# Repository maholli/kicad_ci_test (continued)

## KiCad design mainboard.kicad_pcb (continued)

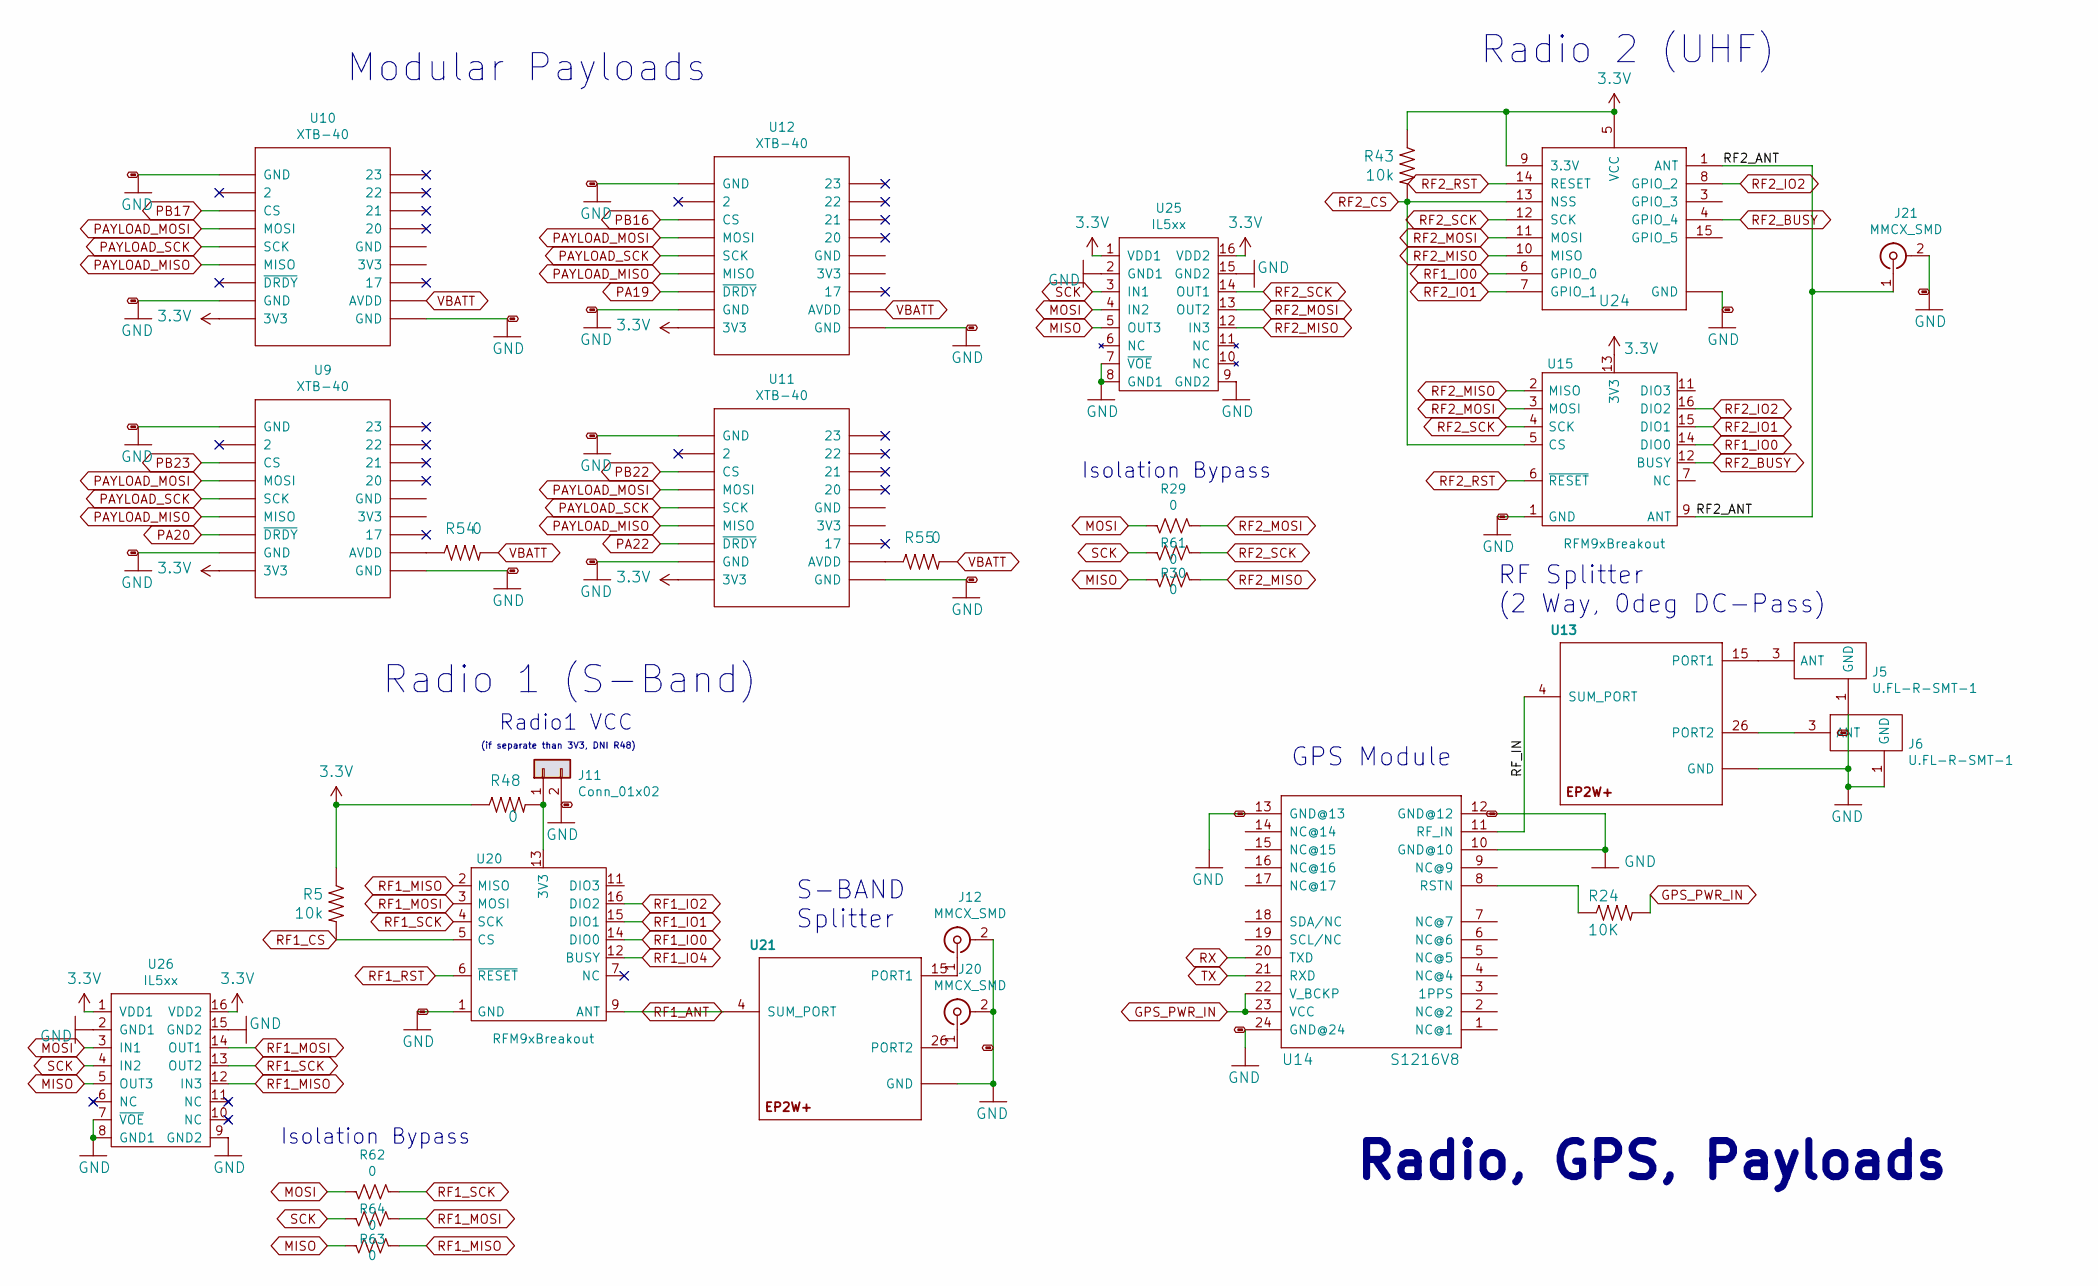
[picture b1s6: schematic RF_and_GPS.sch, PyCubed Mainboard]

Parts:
J5, J6: U.FL-R-SMT-1; Manufacturer_Part_Number U.FL-R-SMT-1
J11: Conn_01x02; PinHeader_1x02_P2.54mm_Vertical
J12, J20, J21: MMCX_SMD; 0734152063
R5, R43: 10k; R_0603_1608Metric
R24: 10K; R_0603_1608Metric
R29, R30, R48, R54, R55, R61, R62, R63, R64: 0; R_0603_1608Metric
U9, U10, U11, U12: XTB-40; XTB28_MEZ
U13, U21: EP2W+; QFN32-5X5MM
U14: S1216V8; S1216_24PIN_PACKAGE
U15, U20: RFM9xBreakout; HOPERF_RFM9XW_SMD
U24: RFM98PW
U25, U26: IL5xx; SOIC-16_IL5xx

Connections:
3.3V: R5.1, R43.1, R48.1, U9.9 (3V3), U10.9 (3V3), U11.9 (3V3), U12.9 (3V3), U15.13 (3V3), U24.5 (VCC), U24.9 (3.3V), U25.1 (VDD1), U25.16 (VDD2), U26.1 (VDD1), U26.16 (VDD2); also elsewhere on the board
/RF and GPS/RF2_ANT: J21.1 (In), U15.9 (ANT), U24.1 (ANT)
/RF and GPS/RF_IN: U13.4 (SUM_PORT), U14.11 (RF_IN)
GND: J5.1 (GND), J5.2, J6.1 (GND), J6.2, J11.2, J12.2 (Ext), J12.3, J12.4, J12.5, J20.2 (Ext), J20.3, J20.4, J20.5, J21.2 (Ext), J21.3, J21.4, J21.5, U9.1 (GND), U9.8 (GND), U9.10 (GND), U9.15 (GND), U10.1 (GND), U10.8 (GND), U10.10 (GND), U10.15 (GND), U11.1 (GND), U11.8 (GND), U11.10 (GND), U11.15 (GND), U12.1 (GND), U12.8 (GND), U12.10 (GND), U12.15 (GND), U13.1 (GND), U13.2 (GND), U13.3 (GND), U13.5 (GND), U13.6 (GND), U13.7 (GND), U13.8 (GND), U13.9 (GND), U13.10 (GND), U13.11 (GND), U13.12 (GND), U13.13 (GND), U13.14 (GND), U13.16 (GND), U13.17 (GND), U13.18 (GND), U13.19 (GND), U13.20 (GND), U13.21 (GND), U13.22 (GND), U13.23 (GND), U13.24 (GND), U13.25 (GND), U13.27 (GND), U13.28 (GND), U13.29 (GND), U13.30 (GND), U13.31 (GND), U13.32 (GND), U13.EP (GND), U14.10 (GND@10), U14.12 (GND@12), U14.13 (GND@13), U14.24 (GND@24), U15.1 (GND), U15.8 (GND), U15.10 (GND), U20.1 (GND), U20.8 (GND), U20.10 (GND), U21.1 (GND), U21.2 (GND), U21.3 (GND), U21.5 (GND), U21.6 (GND), U21.7 (GND), U21.8 (GND), U21.9 (GND), U21.10 (GND), U21.11 (GND), U21.12 (GND), U21.13 (GND), U21.14 (GND), U21.16 (GND), U21.17 (GND), U21.18 (GND), U21.19 (GND), U21.20 (GND), U21.21 (GND), U21.22 (GND), U21.23 (GND), U21.24 (GND), U21.25 (GND), U21.27 (GND), U21.28 (GND), U21.29 (GND), U21.30 (GND), U21.31 (GND), U21.32 (GND), U21.EP (GND), U24.2 (GND), U24.16 (GND), U25.2 (GND1), U25.7 (~VOE), U25.8 (GND1), U25.9 (GND2), U25.15 (GND2), U26.2 (GND1), U26.7 (~VOE), U26.8 (GND1), U26.9 (GND2), U26.15 (GND2); also elsewhere on the board
GPS_PWR_IN: R24.2, U14.22 (V_BCKP), U14.23 (VCC); also elsewhere on the board
MISO: R61.1, R64.1, U25.5 (OUT3), U26.5 (OUT3); also elsewhere on the board
MOSI: R29.1, R62.1, U25.4 (IN2), U26.3 (IN1); also elsewhere on the board
unnamed: J5.3 (ANT), U13.15 (PORT1)
unnamed: J6.3 (ANT), U13.26 (PORT2)
unnamed: J11.1, R48.2, U20.13 (3V3)
unnamed: J12.1 (In), U21.15 (PORT1)
unnamed: J20.1 (In), U21.26 (PORT2)
unnamed: R24.1, U14.8 (RSTN)
unnamed: R54.1, U9.11 (AVDD), U9.16 (AVDD)
unnamed: R55.1, U11.11 (AVDD), U11.16 (AVDD)
PA19: U12.7 (~DRDY); also elsewhere on the board
PA20: U9.7 (~DRDY); also elsewhere on the board
PA22: U11.7 (~DRDY); also elsewhere on the board
PAYLOAD_MISO: U9.6 (MISO), U10.6 (MISO), U11.6 (MISO), U12.6 (MISO); also elsewhere on the board
PAYLOAD_MOSI: U9.4 (MOSI), U10.4 (MOSI), U11.4 (MOSI), U12.4 (MOSI); also elsewhere on the board
PAYLOAD_SCK: U9.5 (SCK), U10.5 (SCK), U11.5 (SCK), U12.5 (SCK); also elsewhere on the board
PB16: U12.3 (CS); also elsewhere on the board
PB17: U10.3 (CS); also elsewhere on the board
PB22: U11.3 (CS); also elsewhere on the board
PB23: U9.3 (CS); also elsewhere on the board
RF1_ANT: U20.9 (ANT), U21.4 (SUM_PORT)
RF1_CS: R5.2, U20.5 (CS); also elsewhere on the board
RF1_IO0: U15.14 (DIO0), U20.14 (DIO0), U24.6 (GPIO_0); also elsewhere on the board
RF1_IO1: U20.15 (DIO1)
RF1_IO2: U20.16 (DIO2)
RF1_IO4: U20.12 (BUSY); also elsewhere on the board
RF1_MISO: R64.2, U20.2 (MISO), U26.12 (IN3)
RF1_MOSI: R63.2, U20.3 (MOSI), U26.14 (OUT1)
RF1_RST: U20.6 (~RESET); also elsewhere on the board
RF1_SCK: R62.2, U20.4 (SCK), U26.13 (OUT2)
RF2_BUSY: U15.12 (BUSY), U24.4 (GPIO_4); also elsewhere on the board
RF2_CS: R43.2, U15.5 (CS), U24.13 (NSS); also elsewhere on the board
RF2_IO1: U15.15 (DIO1), U24.7 (GPIO_1); also elsewhere on the board
RF2_IO2: U15.16 (DIO2), U24.8 (GPIO_2)
RF2_MISO: R61.2, U15.2 (MISO), U24.10 (MISO), U25.12 (IN3); also elsewhere on the board
RF2_MOSI: R29.2, U15.3 (MOSI), U24.11 (MOSI), U25.13 (OUT2); also elsewhere on the board
RF2_RST: U15.6 (~RESET), U24.14 (RESET); also elsewhere on the board
RF2_SCK: R30.2, U15.4 (SCK), U24.12 (SCK), U25.14 (OUT1); also elsewhere on the board
RX: U14.20 (TXD); also elsewhere on the board
SCK: R30.1, R63.1, U25.3 (IN1), U26.4 (IN2); also elsewhere on the board
TX: U14.21 (RXD); also elsewhere on the board
VBATT: R54.2, R55.2, U10.11 (AVDD), U10.16 (AVDD), U12.11 (AVDD), U12.16 (AVDD); also elsewhere on the board

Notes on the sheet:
Modular Payloads
Radio 1 (S-Band)
Isolation Bypass
(if separate than 3V3, DNI R48)
Radio1 VCC
S-BAND Splitter
GPS Module
Radio, GPS, Payloads
Radio 2 (UHF)
RF Splitter (2 Way, 0deg DC-Pass)

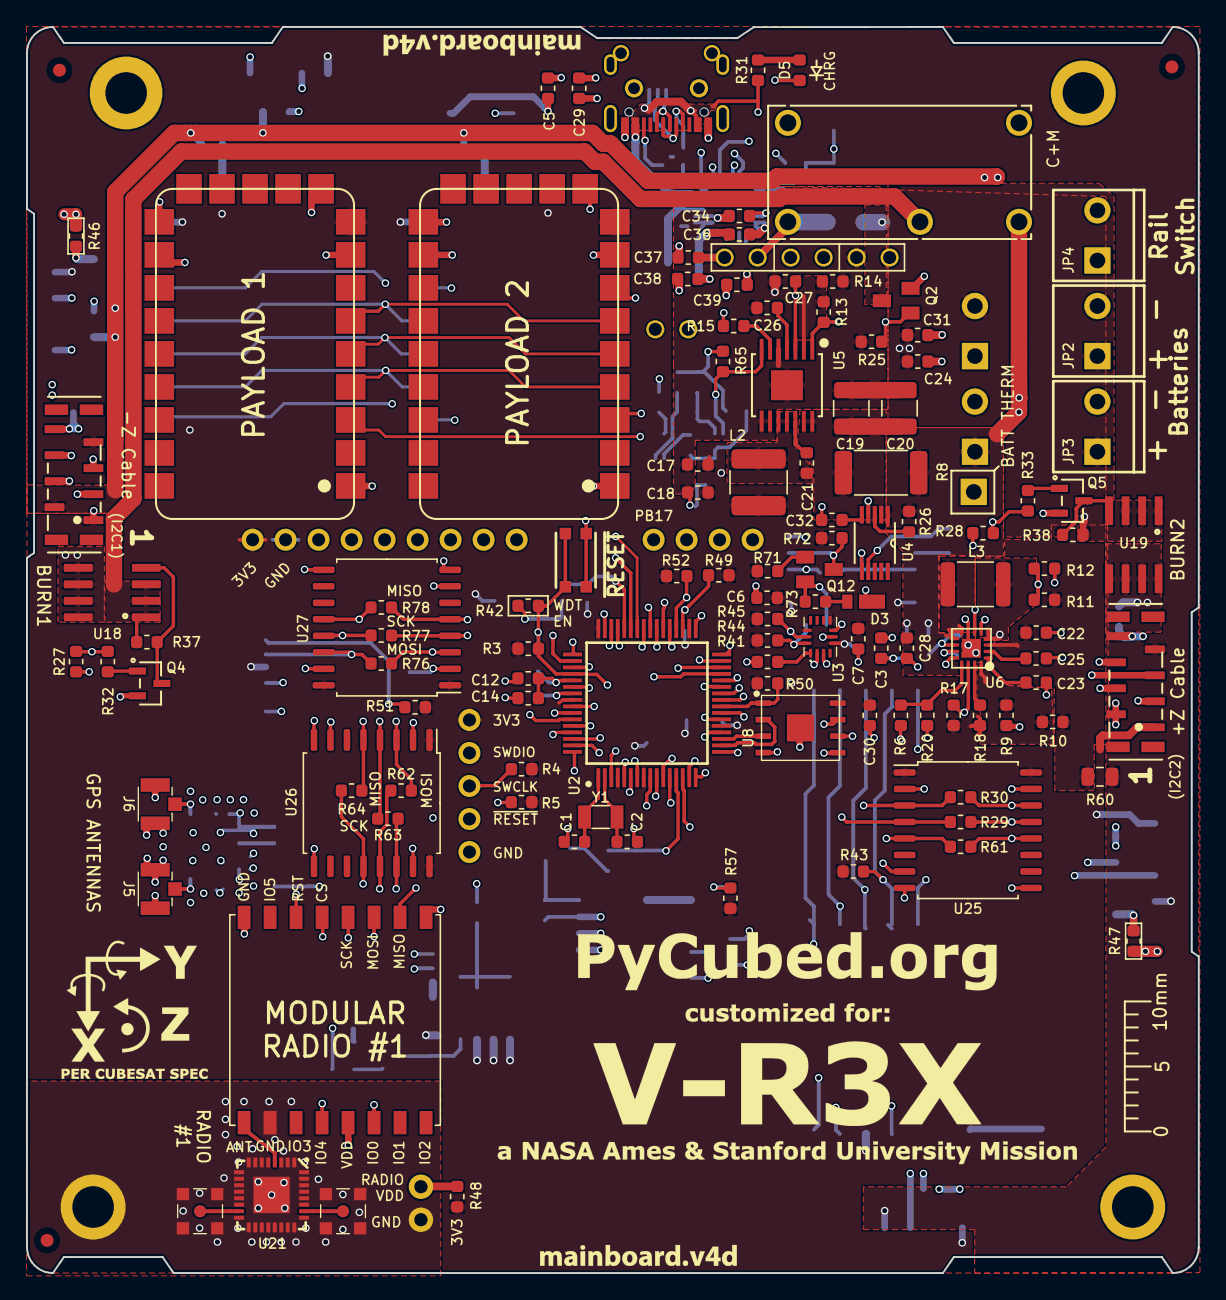
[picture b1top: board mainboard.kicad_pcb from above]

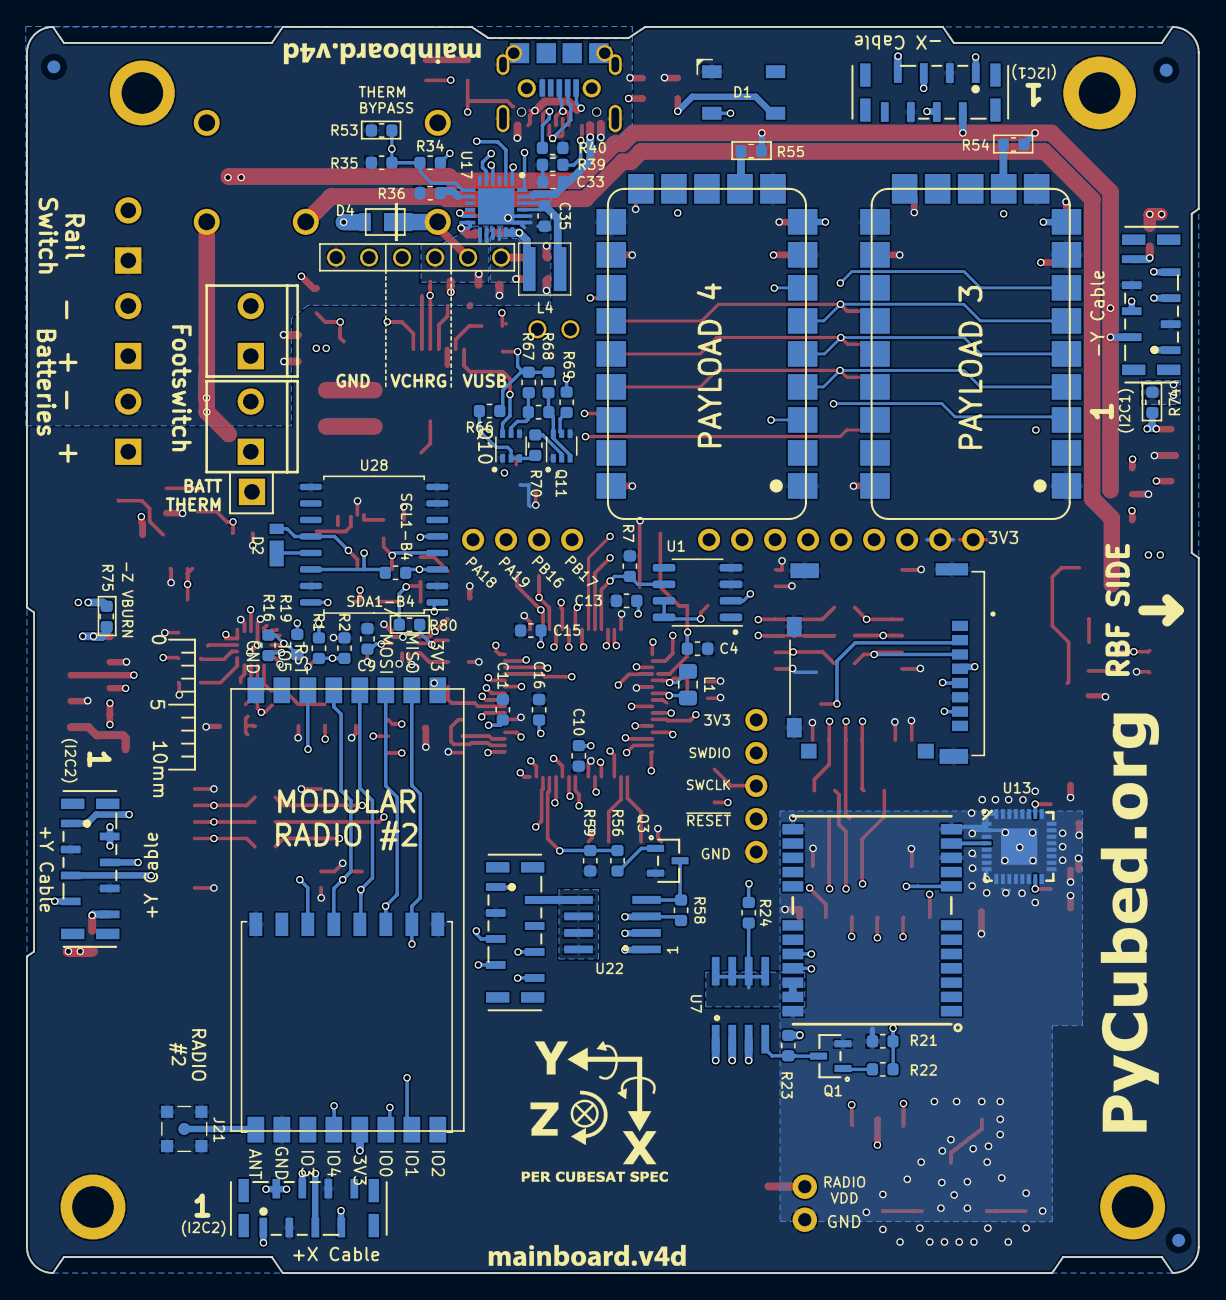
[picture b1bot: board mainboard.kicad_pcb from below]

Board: 4 copper layers, 90.2 x 95.9 mm, 204 parts (72 on the bottom side), 147 nets.

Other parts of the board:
C6: 0.1uF; C_0603_1608Metric
Ref**: Val**; vr3x-mainboard
Ref**#2: Val**; pycubed_twothirds
Ref**#3, Ref**#4, Ref**#5, Ref**#6: Val**; vr3x-version

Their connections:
3.3V: C6.1; also elsewhere on the board
GND: C6.2; also elsewhere on the board

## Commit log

2020-05-06 testing acions
2020-05-06 testing again
2020-05-06 duh.. push paths defined
2020-05-06 timeout fix
2020-05-06 drill output 2 layer
2020-05-06 DRC failed
2020-05-06 zone fill issue?
2020-05-06 random timeout?
2020-05-06 now it should run
2020-05-06 retry
2020-05-06 rollback kiplot.yaml
2020-05-06 error w/ zone fill?
2020-05-06 yes that was the issue
2020-05-06 adding drills
2020-05-06 why didn't it do the gerbers?
2020-05-06 missing quotes?
2020-05-06 forgot to save kiplot.yaml
2020-05-06 why can't it create the directory?
2020-05-06 that worked - trying with sam32 project
2020-05-06 forgot kiplot.yaml
2020-05-06 removing DRC dependency
2020-05-06 SAM32 too jumbled. attempting pycubed
